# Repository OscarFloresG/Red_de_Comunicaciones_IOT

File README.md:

# Red de Comunicaciones IoT para - UABC

Este repositorio contiene el ecosistema de desarrollo de hardware y firmware para la implementación de una red privada de telemetría inalámbrica de largo alcance y bajo consumo, diseñada en vinculación con el Instituto de Ingeniería de la Universidad Autónoma de Baja California (UABC) para el monitoreo de consumo eléctrico en comunidades aisladas (Caso de estudio: Puertecitos, B.C.).

El sistema implementa la tecnología de radiofrecuencia LoRa en la banda libre de 915 MHz, logrando una tasa de pérdida de paquetes muy baja en entornos exteriores a distancias críticas de 300 metros, superando la atenuación por obstáculos físicos y mitigando colisiones por transmisiones concurrentes.

---

## 🛠️ Estructura del Repositorio

* `/placa_lora2`: Archivos de diseño asistido por computadora (CAD) electrónicos correspondientes a la primera etapa de la PCB adaptadora para la integración del transceptor RFM95W y el microcontrolador.
* `/PVVCSMD`: Proyecciones y diseños avanzados de la placa de circuito impreso migrada a tecnología de montaje superficial (SMD) para la optimización de espacio y reducción de costos de fabricación.
* `emisorLora.ino`: Código fuente en C++ para los nodos emisores integrados en los medidores comunitarios. Implementa la estructura de la trama personalizada y el algoritmo de desfasamiento temporal.
* `receptorCentralLora.ino`: Código fuente en C++ para el nodo base centralizador o Gateway encargado de la recepción simultánea, validación de redundancia de errores y puenteo de datos hacia servidores en la nube.

---

## 💻 Descripción de los Códigos de Firmware

### 1. Emisor (`emisorLora.ino`)
Firmware programado para ejecutarse en las unidades remotas de medición. Sus funciones principales son:
* **Estructuración de Trama Propia:** Empaqueta los datos de telemetría bajo un formato optimizado de bajo overhead: `[ID | Seq | Len | Payload | Checksum]` para agilizar el tiempo en el aire (Time-on-Air).
* **Algoritmo de Jitter Aleatorio (Anticolisiones):** Utiliza el ruido electromagnético caótico captado por un pin analógico configurado al aire como semilla para generar un desfasamiento dinámico de +/- 800 ms. Esto evita que los nodos que transmiten simultáneamente bloqueen el canal de comunicación.
* **Control de Errores:** Realiza cálculos de redundancia de datos mediante suma de verificación XOR por software antes de enviar el paquete por el transceptor.

### 2. Receptor Central (`receptorCentralLora.ino`)
Firmware dedicado al Gateway o nodo base de recolección local. Sus funciones principales son:
* **Escucha Concurrente y Modulación:** Configura el módulo de radio bajo parámetros de alta sensibilidad en la frecuencia de 915 MHz, Ancho de Banda (BW) de 125 kHz y Factor de Ensanchamiento (SF) de 7.
* **Doble Validación de Integridad:** Corrobora la exactitud de los bits recibidos mediante el análisis combinado de CRC por hardware y la verificación XOR por software, descartando tramas corruptas provocadas por interferencias del entorno.
* **Métricas de Diagnóstico:** Extrae y evalúa en tiempo real los valores de RSSI (Indicador de Fuerza de Señal Recibida) y SNR (Relación Señal-Ruido) para el diagnóstico físico del enlace.

---

## 📡 Especificaciones de Radiofrecuencia (RF)
* **Tecnología:** LoRa (Chipset Semtech SX1276 / RFM95W)
* **Frecuencia:** 915 MHz (Banda ISM libre para México)
* **Ancho de Banda (BW):** 125 kHz
* **Spreading Factor (SF):** 7
* **Potencia de Salida:** 17 dBm (50 mW)

---

## 👥 Desarrolladores
* Diego Castañeda Covarrubias
* Oscar Eduardo Flores García
* Herick Gerardo Vizcarra Macías

*Proyecto de Vinculación con Valor en Créditos (PVVC) bajo la mentoría del Dr. Saúl - Laboratorio de Energías Renovables, Instituto de Ingeniería de la UABC.*

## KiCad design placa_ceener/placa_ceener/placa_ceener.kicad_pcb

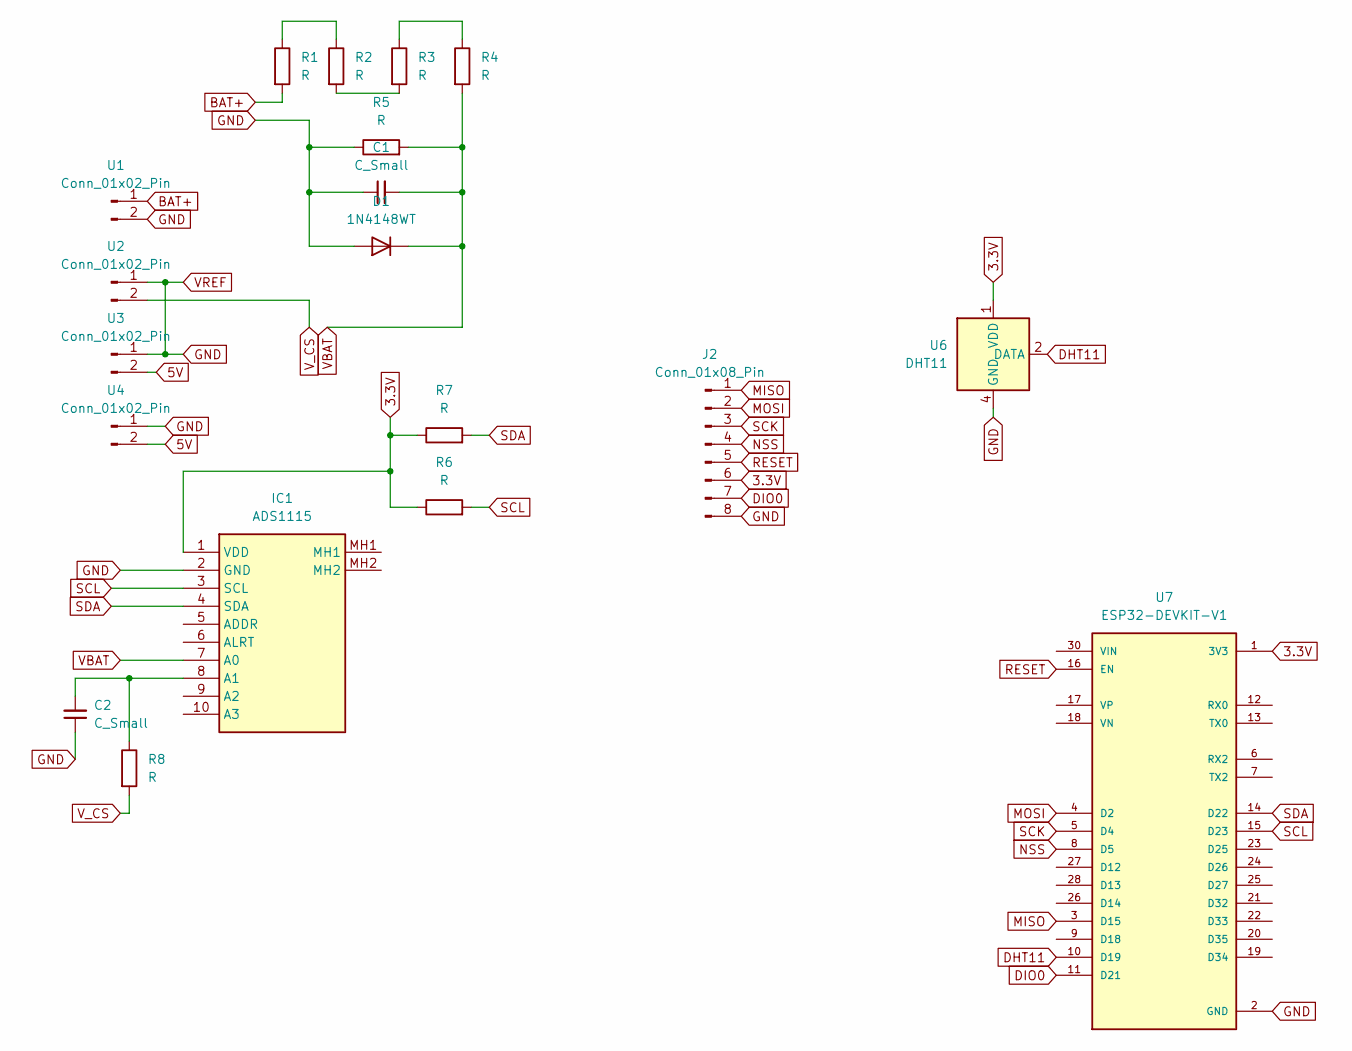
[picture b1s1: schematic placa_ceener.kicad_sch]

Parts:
C1, C2: C_Small; C_Axial_L3.8mm_D2.6mm_P7.50mm_Horizontal
D1: 1N4148WT; D_DO-34_SOD68_P5.08mm_Vertical_KathodeUp
IC1: ADS1115; Manufacturer_Part_Number ADS1115
J2: Conn_01x08_Pin; PinHeader_1x08_P2.54mm_Vertical
R1, R2, R3, R4, R5, R6, R7, R8: R; R_Axial_DIN0204_L3.6mm_D1.6mm_P5.08mm_Horizontal
U1, U2, U3, U4: Conn_01x02_Pin; TerminalBlock_4Ucon_1x02_P3.50mm_Horizontal
U6: DHT11; Aosong_DHT11_5.5x12.0_P2.54mm
U7: ESP32-DEVKIT-V1; MODULE_ESP32_DEVKIT_V1; PARTREV N/A

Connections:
3.3V: IC1.1 (VDD), J2.6, R6.1, R7.1, U6.1 (VDD), U7.1 (3V3)
5V: U3.2, U4.2
BAT+: R1.2, U1.1
DHT11: U6.2 (DATA), U7.10 (D19)
DIO0: J2.7, U7.11 (D21)
GND: C1.1, C2.1, D1.2 (A), IC1.2 (GND), J2.8, R5.1, U1.2, U2.1, U3.1, U4.1, U6.4 (GND), U7.2 (GND), U7.29 (GND)
MISO: J2.1, U7.3 (D15)
MOSI: J2.2, U7.4 (D2)
NSS: J2.4, U7.8 (D5)
unnamed: C2.2, IC1.8 (A1), R8.1
unnamed: R1.1, R2.1
unnamed: R2.2, R3.2
unnamed: R3.1, R4.1
RESET: J2.5, U7.16 (EN)
SCK: J2.3, U7.5 (D4)
SCL: IC1.3 (SCL), R6.2, U7.15 (D23)
SDA: IC1.4 (SDA), R7.2, U7.14 (D22)
VBAT: C1.2, D1.1 (K), IC1.7 (A0), R4.2, R5.2
V_CS: R8.2, U2.2

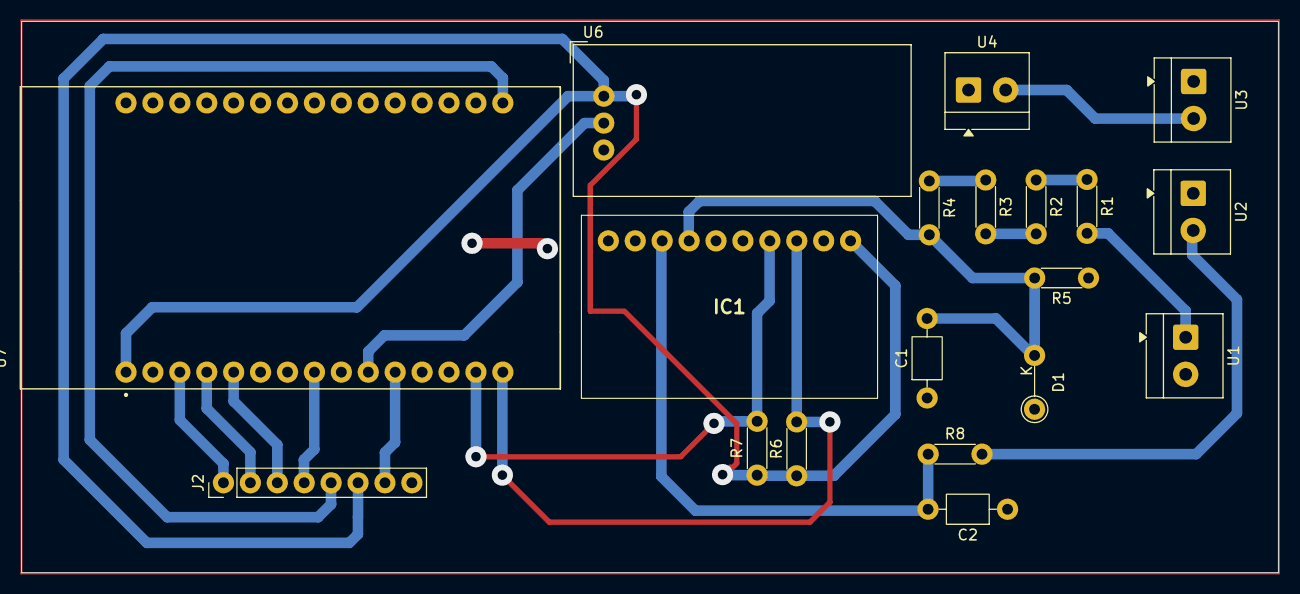
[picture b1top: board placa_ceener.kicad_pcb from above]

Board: 2 copper layers, 118.6 x 52.0 mm, 19 parts (0 on the bottom side), 19 nets.

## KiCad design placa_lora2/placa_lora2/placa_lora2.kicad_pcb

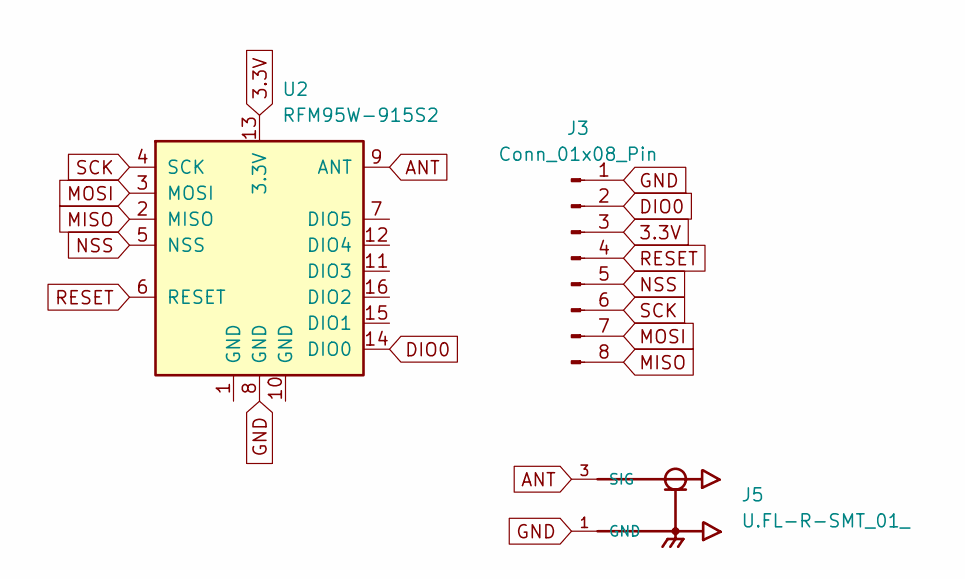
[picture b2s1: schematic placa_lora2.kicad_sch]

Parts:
J3: Conn_01x08_Pin; PinHeader_1x08_P2.54mm_Vertical
J5: U.FL-R-SMT_01_; HRS_U.FL-R-SMT_01_
U2: RFM95W-915S2; HOPERF_RFM9XW_SMD

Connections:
3.3V: J3.3, U2.13 (3.3V)
ANT: J5.3 (SIG), U2.9 (ANT)
DIO0: J3.2, U2.14 (DIO0)
GND: J3.1, J5.1 (GND), J5.2 (GND), U2.8 (GND)
MISO: J3.8, U2.2 (MISO)
MOSI: J3.7, U2.3 (MOSI)
NSS: J3.5, U2.5 (NSS)
RESET: J3.4, U2.6 (RESET)
SCK: J3.6, U2.4 (SCK)

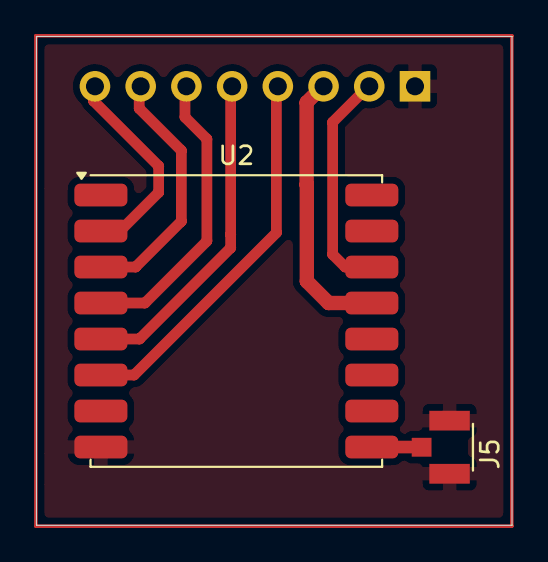
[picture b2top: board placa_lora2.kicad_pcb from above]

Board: 2 copper layers, 26.4 x 27.2 mm, 3 parts (1 on the bottom side), 9 nets.

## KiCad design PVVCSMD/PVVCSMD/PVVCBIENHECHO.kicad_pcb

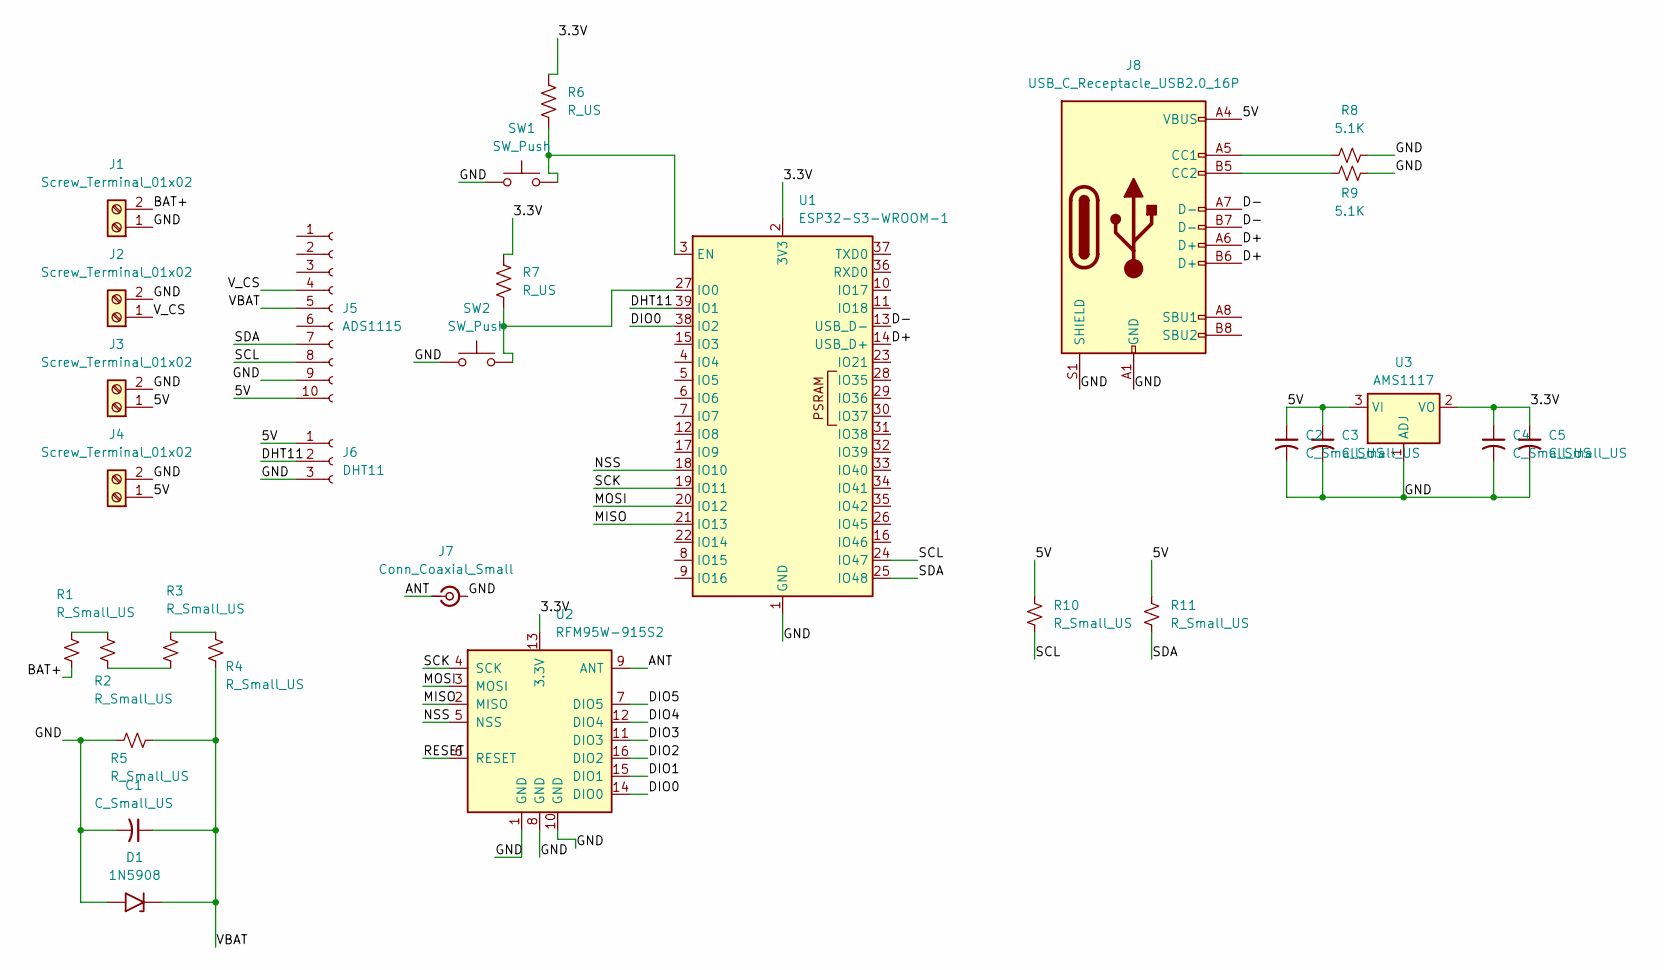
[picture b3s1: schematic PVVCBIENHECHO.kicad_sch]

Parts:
C1, C2, C3, C4, C5: C_Small_US; C_1206_3216Metric
D1: 1N5908; D_1206_3216Metric
J1, J2, J3, J4: Screw_Terminal_01x02; TerminalBlock_Xinya_XY308-2.54-2P_1x02_P2.54mm_Horizontal
J5: ADS1115; PinSocket_1x10_P2.54mm_Vertical
J6: DHT11; PinSocket_1x03_P2.54mm_Vertical
J7: Conn_Coaxial_Small; U.FL_Hirose_U.FL-R-SMT-1_Vertical
J8: USB_C_Receptacle_USB2.0_16P; USB_C_Receptacle_HRO_TYPE-C-31-M-12
R1, R2, R3, R4, R5, R10, R11: R_Small_US; R_1206_3216Metric
R6, R7: R_US; R_1206_3216Metric
R8, R9: 5.1K; R_1206_3216Metric
SW1, SW2: SW_Push; SW_PUSH_6mm_H8mm
U1: ESP32-S3-WROOM-1
U2: RFM95W-915S2; HOPERF_RFM9XW_SMD
U3: AMS1117; SOT-223-3_TabPin2

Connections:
/3.3V: C4.1, C5.1, R6.1, R7.1, U1.2 (3V3), U2.13 (3.3V), U3.2 (VO)
/5V: C2.1, C3.1, J3.1, J4.1, J5.10, J6.1, J8.A4 (VBUS), J8.A9 (VBUS), J8.B4 (VBUS), J8.B9 (VBUS), R10.1, R11.1, U3.3 (VI)
/ANT: J7.1 (In), U2.9 (ANT)
/BAT+: J1.2, R1.2
/D+: J8.A6 (D+), J8.B6 (D+), U1.14 (USB_D+)
/D-: J8.A7 (D-), J8.B7 (D-), U1.13 (USB_D-)
/DHT11: J6.2, U1.39 (IO1)
/DIO0: U1.38 (IO2), U2.14 (DIO0)
/DIO1: U2.15 (DIO1)
/DIO2: U2.16 (DIO2)
/DIO3: U2.11 (DIO3)
/DIO4: U2.12 (DIO4)
/DIO5: U2.7 (DIO5)
/GND: C1.2, C2.2, C3.2, C4.2, C5.2, D1.2 (A2), J1.1, J2.2, J3.2, J4.2, J5.9, J6.3, J7.2 (Ext), J8.A1 (GND), J8.A12 (GND), J8.B1 (GND), J8.B12 (GND), J8.S1 (SHIELD), R5.2, R8.2, R9.2, SW1.1, SW2.1, U1.1 (GND), U1.40 (GND), U1.41 (GND), U2.1 (GND), U2.8 (GND), U2.10 (GND), U3.1 (ADJ)
/MISO: U1.21 (IO13), U2.2 (MISO)
/MOSI: U1.20 (IO12), U2.3 (MOSI)
/NSS: U1.18 (IO10), U2.5 (NSS)
/RESET: U2.6 (RESET)
/SCK: U1.19 (IO11), U2.4 (SCK)
/SCL: J5.8, R10.2, U1.24 (IO47)
/SDA: J5.7, R11.2, U1.25 (IO48)
/VBAT: C1.1, D1.1 (A1), J5.5, R4.2, R5.1
/V_CS: J2.1, J5.4
unnamed: J8.A5 (CC1), R8.1
unnamed: J8.B5 (CC2), R9.1
unnamed: R1.1, R2.1
unnamed: R2.2, R3.2
unnamed: R3.1, R4.1
unnamed: R6.2, SW1.2, U1.3 (EN)
unnamed: R7.2, SW2.2, U1.27 (IO0)

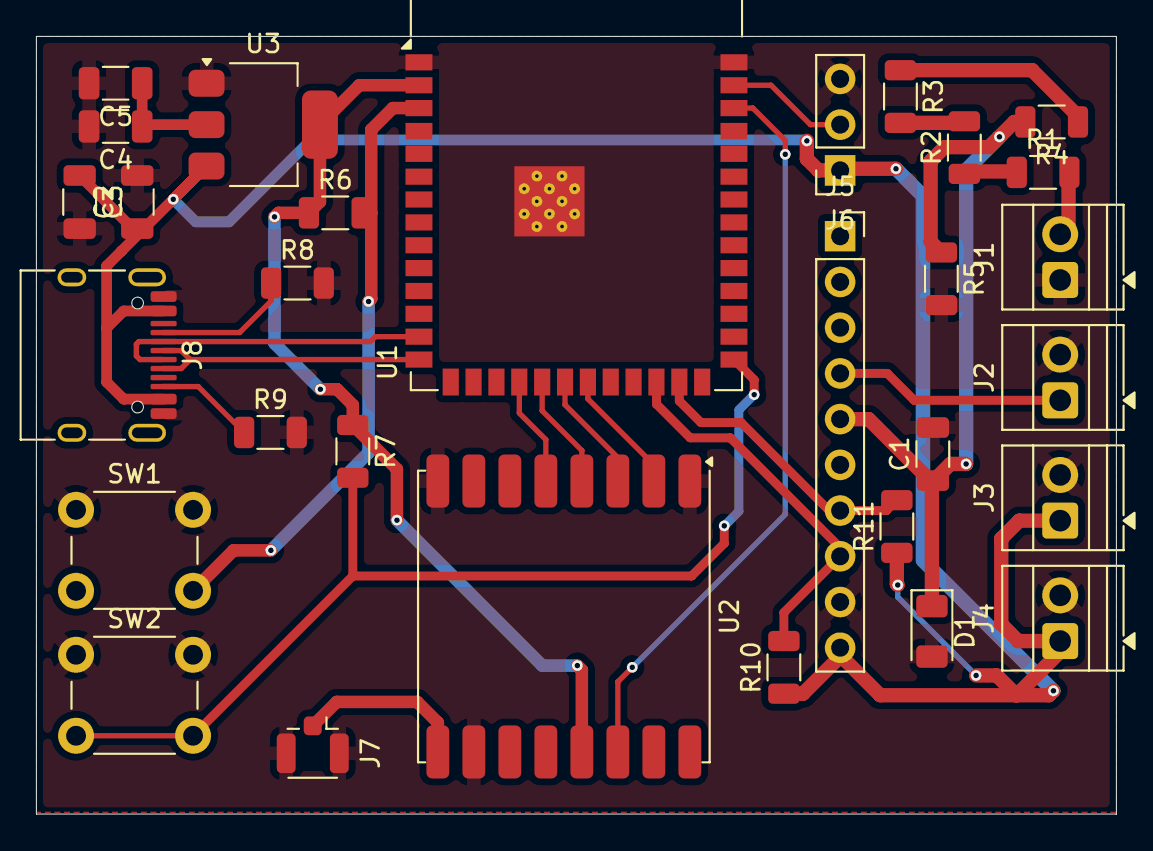
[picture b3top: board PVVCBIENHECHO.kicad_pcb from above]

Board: 2 copper layers, 60.0 x 43.2 mm, 30 parts (0 on the bottom side), 24 nets.

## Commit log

2026-05-29 Proyecto KiCad con diseño de componentes SMD
2026-05-29 Diseño de Placa con los componentes SMD
2026-06-03 Codigos apra comunicacion lora
    Archivos .ino con codigos para lora emisor y receptor.
2026-06-05 Diseño PCB del módulo LoRa
2026-06-05 Revise README for project overview and details
    Updated the README to provide detailed project information and structure.
2026-06-05 Diseño de su circuito con el módulo adaptador.
